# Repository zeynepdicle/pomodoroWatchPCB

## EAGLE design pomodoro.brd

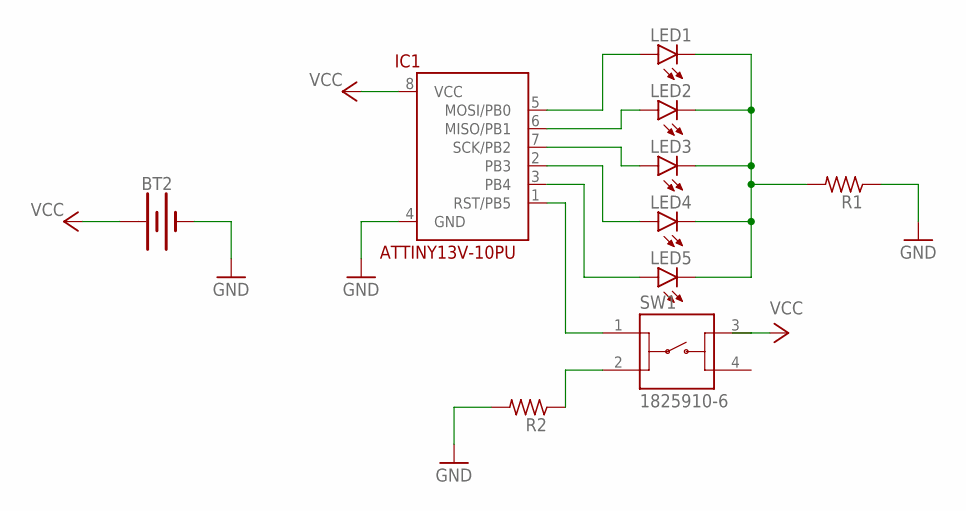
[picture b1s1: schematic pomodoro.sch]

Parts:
BT2: BATTERY-20MM_PTH_KIT; BATTCOM_20MM_PTH_KIT
IC1: ATTINY13V-10PU; DIL08
LED1, LED2, LED3, LED4, LED5: LED3MM
R1, R2: R-US_0204/7; 0204/7
SW1: 1825910-6

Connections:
GND: BT2.2 (-), IC1.4 (GND), R1.1, R2.2
unnamed: IC1.5 (MOSI/PB0), LED1.A
unnamed: IC1.6 (MISO/PB1), LED2.A
unnamed: IC1.7 (SCK/PB2), LED3.A
unnamed: IC1.2 (PB3), LED4.A
unnamed: IC1.3 (PB4), LED5.A
unnamed: LED1.K (C), LED2.K (C), LED3.K (C), LED4.K (C), LED5.K (C), R1.2
unnamed: IC1.1 (RST/PB5), SW1.1
unnamed: R2.1, SW1.2
VCC: BT2.1 (+), IC1.8 (VCC), SW1.3

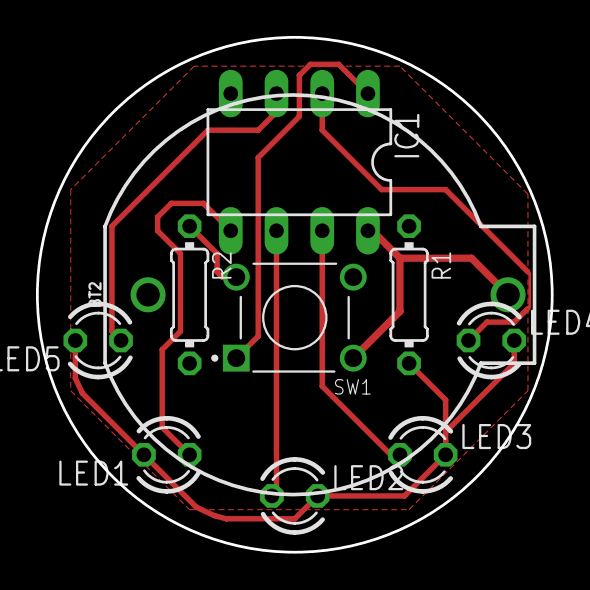
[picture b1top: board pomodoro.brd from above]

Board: 2 copper layers, 28.6 x 28.6 mm, 10 parts (0 on the bottom side), 10 nets.

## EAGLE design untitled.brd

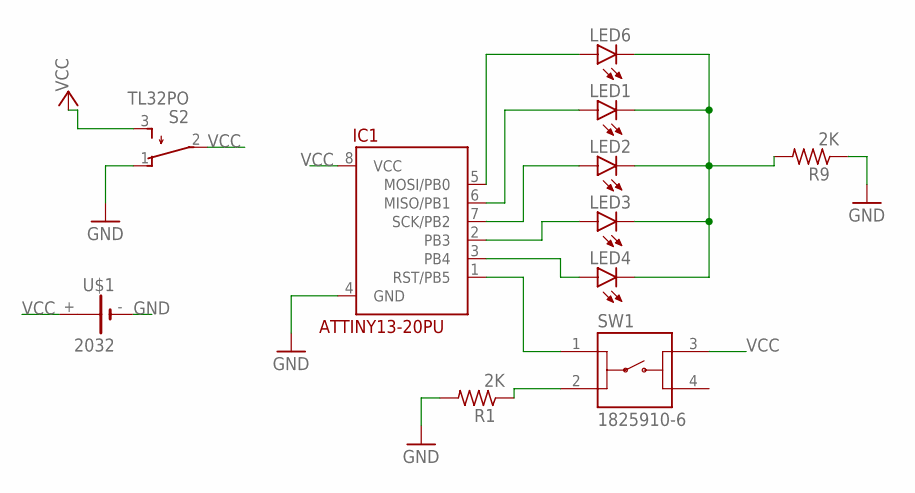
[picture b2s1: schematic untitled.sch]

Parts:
IC1: ATTINY13-20PU; DIL08
LED1, LED2, LED3, LED4, LED6: LED3MM
R1, R9: 2K; 0204/7
S2: TL32PO; TL3XPO
SW1: 1825910-6
U$1: 2032; KZH20SMD

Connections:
GND: IC1.4 (GND), R1.2, R9.1, S2.1 (O), U$1.-
unnamed: IC1.5 (MOSI/PB0), LED6.A
unnamed: IC1.6 (MISO/PB1), LED1.A
unnamed: IC1.7 (SCK/PB2), LED2.A
unnamed: IC1.2 (PB3), LED3.A
unnamed: IC1.3 (PB4), LED4.A
unnamed: LED1.K (C), LED2.K (C), LED3.K (C), LED4.K (C), LED6.K (C), R9.2
unnamed: IC1.1 (RST/PB5), SW1.1
unnamed: R1.1, SW1.2
VCC: IC1.8 (VCC), S2.2, S2.3 (S), SW1.3, U$1.+

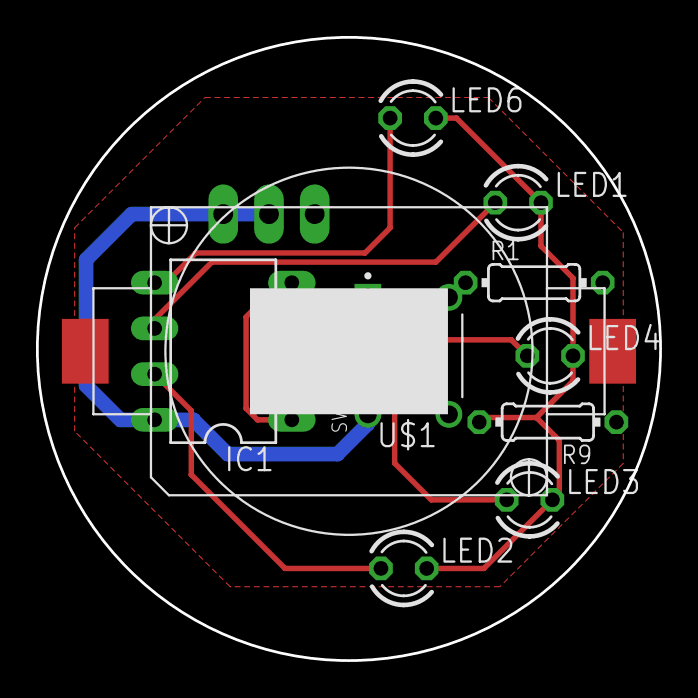
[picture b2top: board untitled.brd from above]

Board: 2 copper layers, 34.6 x 34.6 mm, 11 parts (1 on the bottom side), 10 nets.

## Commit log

2020-06-21 first circuit drawing
2020-06-23 errors fixed
2020-07-22 the circuit was redrawn
2020-07-24 curcuit changed

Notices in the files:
parts and their libraries:
SparkFun-Batteries: Licensing: Creative Commons ShareAlike 4.0 International - https://creativecommons.org/licenses/by-sa/4.0
